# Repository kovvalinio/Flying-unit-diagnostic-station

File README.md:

# Flying-unit-diagnostic-station
This is the development repository for the embedded system created by me and Adam Polus as a diploma thesis.
The goal is to create the system that will collect data from sensors and pass them wirlessly to PC. 
The system will be attached to a drone and will constantly provide data from accelerometers and microphones.
Data will held the information about vibrations generated by motors.

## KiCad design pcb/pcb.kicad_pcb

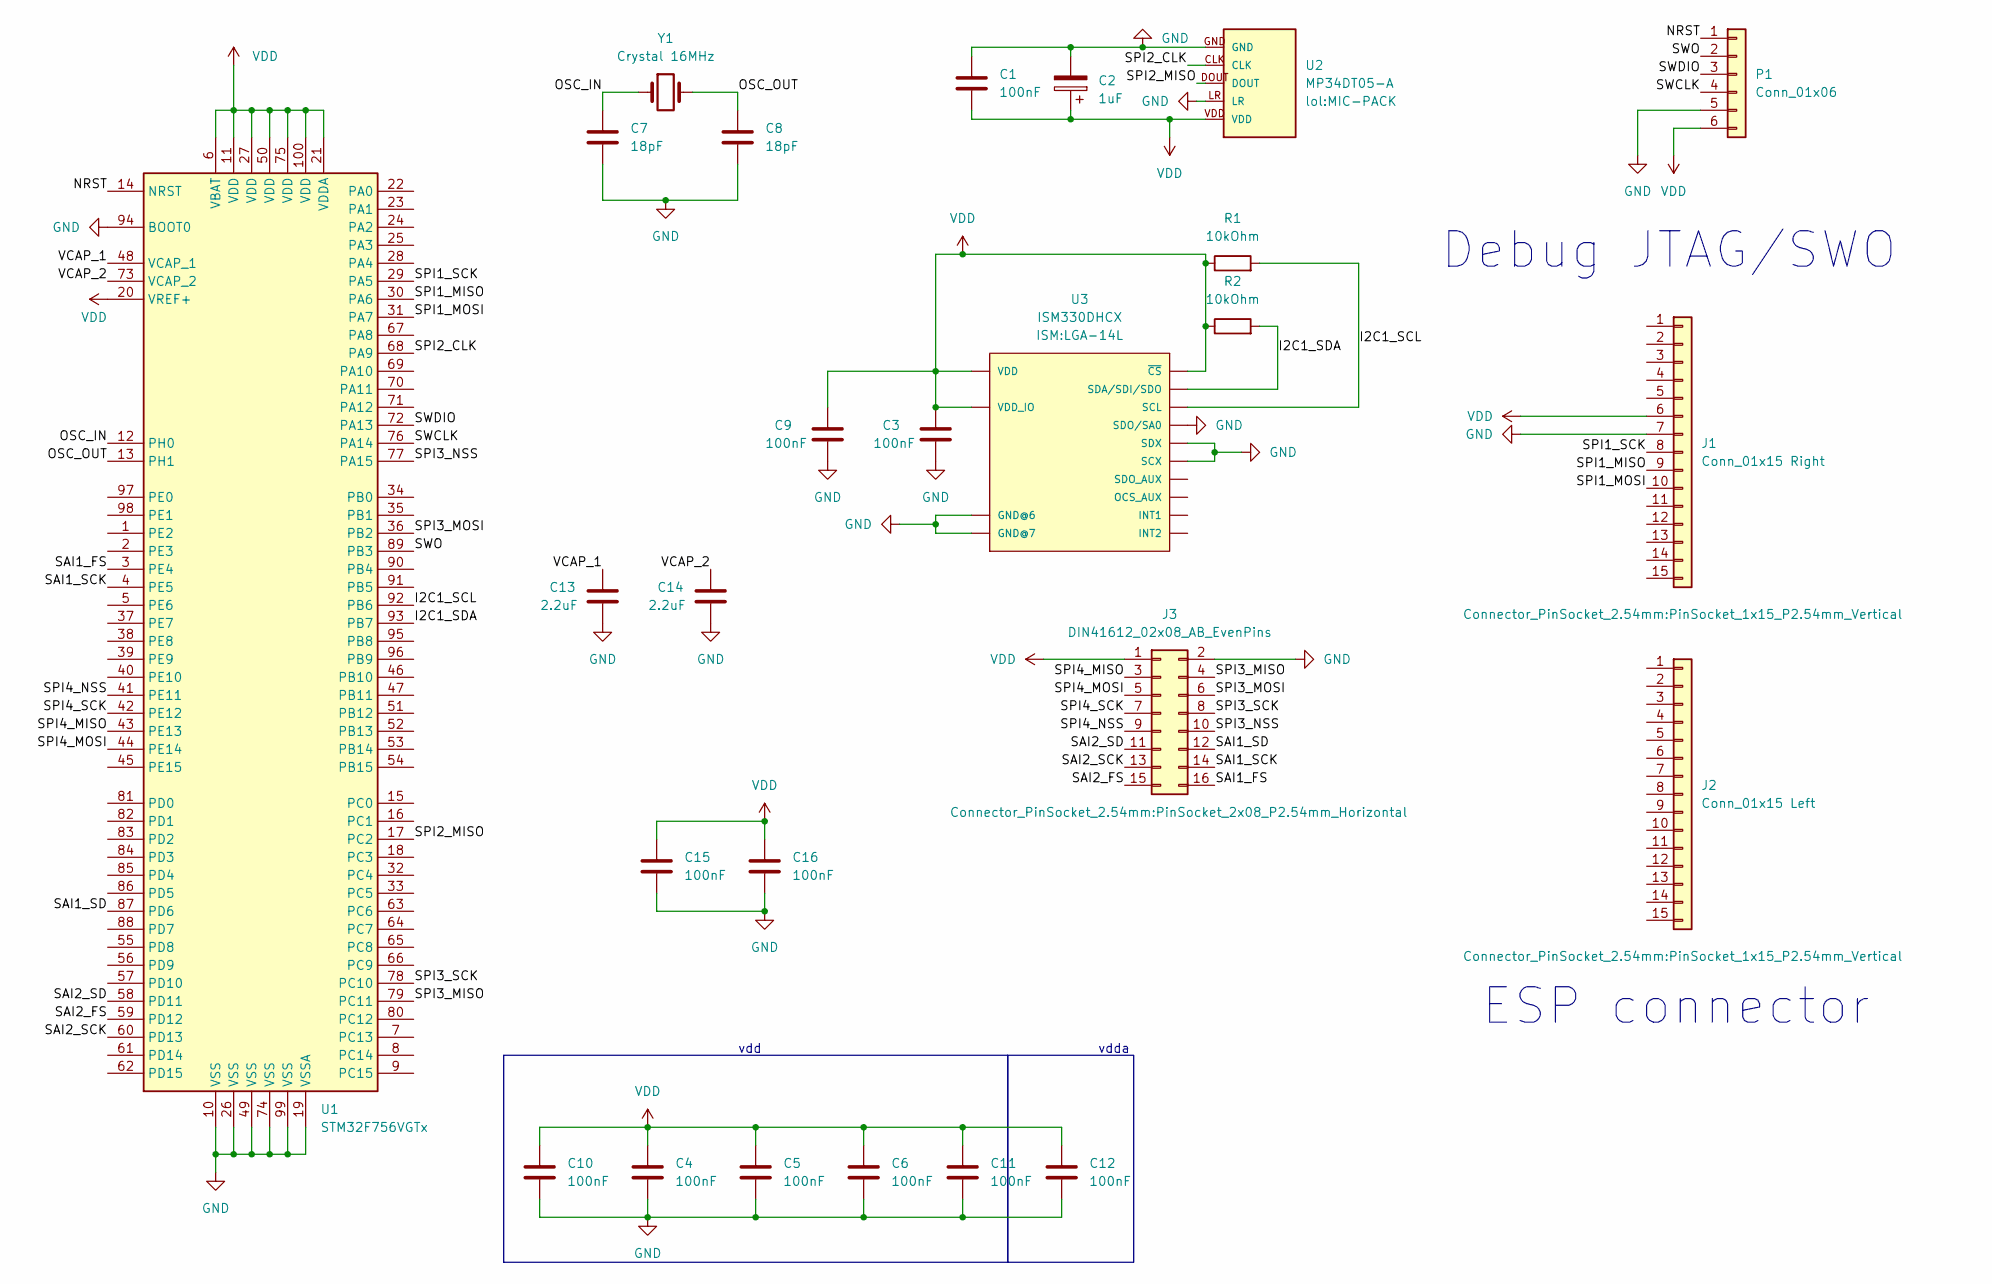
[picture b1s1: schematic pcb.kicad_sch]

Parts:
C1, C4, C5, C6, C10, C11, C12, C15, C16: 100nF; C_0603_1608Metric
C2: 1uF; C_0603_1608Metric
C3, C9: 100nF; R_0603_1608Metric
C7, C8: 18pF; C_0603_1608Metric
C13, C14: 2.2uF; R_0603_1608Metric
J1: Conn_01x15 Right; PinSocket_1x15_P2.54mm_Vertical
J2: Conn_01x15 Left; PinSocket_1x15_P2.54mm_Vertical
J3: DIN41612_02x08_AB_EvenPins; PinSocket_2x08_P2.54mm_Horizontal
P1: Conn_01x06; Molex_PicoBlade_53047-0610_1x06_P1.25mm_Vertical
R1, R2: 10kOhm; R_0603_1608Metric
U1: STM32F756VGTx; LQFP-100_14x14mm_P0.5mm
U2: MP34DT05-A; MIC-PACK
U3: ISM330DHCX; LGA-14L
Y1: Crystal 16MHz; Crystal_SMD_Abracon_ABM3-2Pin_5.0x3.2mm

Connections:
/I2C1_SCL: R1.2, U1.92 (PB6), U3.P13 (SCL)
/I2C1_SDA: R2.2, U1.93 (PB7), U3.P14 (SDA/SDI/SDO)
/NRST: P1.1, U1.14 (NRST)
/OSC_IN: C7.2, U1.12 (PH0), Y1.1
/OSC_OUT: C8.2, U1.13 (PH1), Y1.2
/SAI1_FS: J3.16 (Pin_b16), U1.3 (PE4)
/SAI1_SCK: J3.14 (Pin_b14), U1.4 (PE5)
/SAI1_SD: J3.12 (Pin_b12), U1.87 (PD6)
/SAI2_FS: J3.15 (Pin_a16), U1.59 (PD12)
/SAI2_SCK: J3.13 (Pin_a14), U1.60 (PD13)
/SAI2_SD: J3.11 (Pin_a12), U1.58 (PD11)
/SPI1_MISO: J1.9, U1.30 (PA6)
/SPI1_MOSI: J1.10, U1.31 (PA7)
/SPI1_SCK: J1.8, U1.29 (PA5)
/SPI2_CLK: U1.68 (PA9), U2.CLK
/SPI2_MISO: U1.17 (PC2), U2.DOUT
/SPI3_MISO: J3.4 (Pin_b4), U1.79 (PC11)
/SPI3_MOSI: J3.6 (Pin_b6), U1.36 (PB2)
/SPI3_NSS: J3.10 (Pin_b10), U1.77 (PA15)
/SPI3_SCK: J3.8 (Pin_b8), U1.78 (PC10)
/SPI4_MISO: J3.3 (Pin_a4), U1.43 (PE13)
/SPI4_MOSI: J3.5 (Pin_a6), U1.44 (PE14)
/SPI4_NSS: J3.9 (Pin_a10), U1.41 (PE11)
/SPI4_SCK: J3.7 (Pin_a8), U1.42 (PE12)
/SWCLK: P1.4, U1.76 (PA14)
/SWDIO: P1.3, U1.72 (PA13)
/SWO: P1.2, U1.89 (PB3)
/VCAP_1: C13.1, U1.48 (VCAP_1)
/VCAP_2: C14.1, U1.73 (VCAP_2)
GND: C1.2, C2.2, C3.2, C4.1, C5.1, C6.1, C7.1, C8.1, C9.2, C10.1, C11.1, C12.1, C13.2, C14.2, C15.1, C16.1, J1.7, J3.2 (Pin_b2), P1.5, U1.10 (VSS), U1.19 (VSSA), U1.26 (VSS), U1.49 (VSS), U1.74 (VSS), U1.94 (BOOT0), U1.99 (VSS), U2.GND, U2.LR, U3.P1 (SDO/SA0), U3.P2 (SDX), U3.P3 (SCX), U3.P6 (GND@6), U3.P7 (GND@7)
VDD: C1.1, C2.1, C3.1, C4.2, C5.2, C6.2, C9.1, C10.2, C11.2, C12.2, C15.2, C16.2, J1.6, J3.1 (Pin_a2), P1.6, R1.1, R2.1, U1.6 (VBAT), U1.11 (VDD), U1.20 (VREF+), U1.21 (VDDA), U1.27 (VDD), U1.50 (VDD), U1.75 (VDD), U1.100 (VDD), U2.VDD, U3.P5 (VDD_IO), U3.P8 (VDD), U3.P12 (~CS)

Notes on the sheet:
ESP connector
vdd
Debug JTAG/SWO
vdda

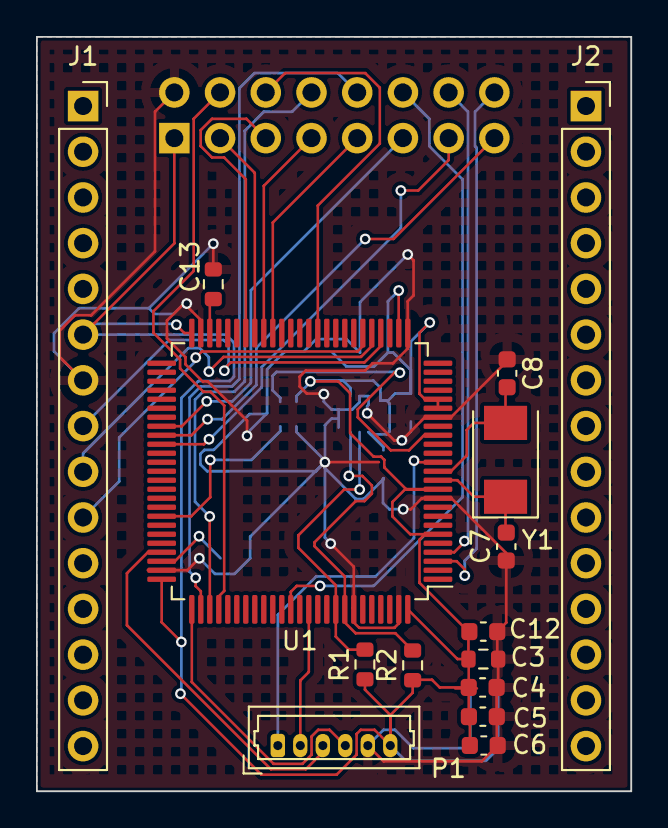
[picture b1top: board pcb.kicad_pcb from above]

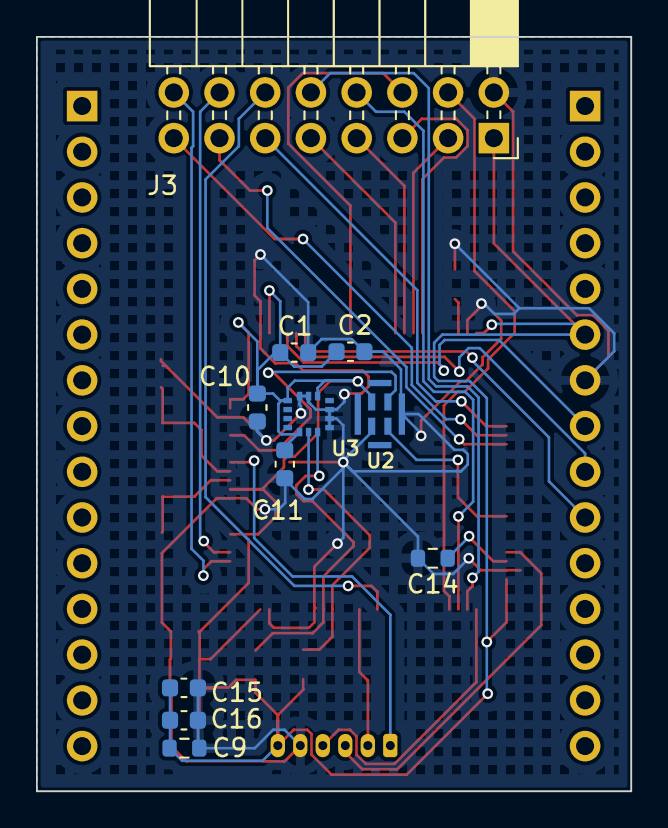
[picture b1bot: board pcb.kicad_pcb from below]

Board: 2 copper layers, 33.0 x 41.9 mm, 26 parts (11 on the bottom side), 31 nets.

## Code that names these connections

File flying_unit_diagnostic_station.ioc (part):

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Mcu.Name=STM32F767ZITx
Mcu.Package=LQFP144
Mcu.UserName=STM32F767ZITx
PA1.GPIOParameters=GPIO_Label
PA1.GPIO_Label=RMII_REF_CLK [LAN8742A-CZ-TR_REFCLK0]
PA1.Signal=ETH_REF_CLK
PA10.GPIOParameters=GPIO_Label
PA10.GPIO_Label=USB_ID
PA10.Signal=USB_OTG_FS_ID
PA11.GPIOParameters=GPIO_Label
PA11.GPIO_Label=USB_DM
PA11.Signal=USB_OTG_FS_DM
PA12.GPIOParameters=GPIO_Label
PA12.GPIO_Label=USB_DP
PA12.Signal=USB_OTG_FS_DP
PA13.GPIOParameters=GPIO_Label
PA13.GPIO_Label=TMS
PA13.Mode=Serial_Wire
PA13.Signal=SYS_JTMS-SWDIO
PA14.GPIOParameters=GPIO_Label
PA14.GPIO_Label=TCK
PA14.Mode=Serial_Wire
PA14.Signal=SYS_JTCK-SWCLK
PA2.GPIOParameters=GPIO_Label
PA2.GPIO_Label=RMII_MDIO [LAN8742A-CZ-TR_MDIO]
PA2.Signal=ETH_MDIO
PA4.Mode=Half_Duplex_Master
PA4.Signal=I2S1_WS
PA5.Mode=Half_Duplex_Master
PA5.Signal=I2S1_CK
PA7.GPIOParameters=GPIO_Label
PA7.GPIO_Label=RMII_CRS_DV [LAN8742A-CZ-TR_CRS_DV]
PA7.Signal=ETH_CRS_DV
PA8.GPIOParameters=GPIO_Label
PA8.GPIO_Label=USB_SOF [TP1]
PA8.Signal=USB_OTG_FS_SOF
PA9.GPIOParameters=GPIO_Label
PA9.GPIO_Label=USB_VBUS
PA9.Signal=USB_OTG_FS_VBUS
PB0.GPIOParameters=GPIO_Label
PB0.GPIO_Label=LD1 [Green]
PB0.Signal=GPIO_Output
PB13.GPIOParameters=GPIO_Label
PB13.GPIO_Label=RMII_TXD1 [LAN8742A-CZ-TR_TXD1]
PB13.Signal=ETH_TXD1
PB14.GPIOParameters=GPIO_Label
PB14.GPIO_Label=LD3 [Red]
PB14.Signal=GPIO_Output
PB3.GPIOParameters=GPIO_Label
PB3.GPIO_Label=SWO
PB3.Signal=SYS_JTDO-SWO
PB7.GPIOParameters=GPIO_Label
PB7.GPIO_Label=LD2 [Blue]
PB7.Signal=GPIO_Output
PB8.Mode=I2C
PB8.Signal=I2C1_SCL
PB9.Mode=I2C
PB9.Signal=I2C1_SDA
PC1.GPIOParameters=GPIO_Label
PC1.GPIO_Label=RMII_MDC [LAN8742A-CZ-TR_MDC]
PC1.Signal=ETH_MDC
PC13.GPIOParameters=GPIO_Label
PC13.GPIO_Label=USER_Btn [B1]
PC13.Signal=GPXTI13
PC14/OSC32_IN.Mode=LSE-External-Oscillator
PC14/OSC32_IN.Signal=RCC_OSC32_IN
PC15/OSC32_OUT.Mode=LSE-External-Oscillator
PC15/OSC32_OUT.Signal=RCC_OSC32_OUT
PC5.GPIOParameters=GPIO_Label
PC5.GPIO_Label=RMII_RXD1 [LAN8742A-CZ-TR_RXD1]
PC5.Signal=ETH_RXD1
PD7.Mode=Half_Duplex_Master
PD7.Signal=I2S1_SD
PD8.GPIOParameters=GPIO_Label
PD8.GPIO_Label=STLK_RX [STM32F103CBT6_PA3]
PD8.Mode=Asynchronous
PD8.Signal=USART3_TX
PD9.GPIOParameters=GPIO_Label
PD9.GPIO_Label=STLK_TX [STM32F103CBT6_PA2]
PD9.Mode=Asynchronous
PD9.Signal=USART3_RX
PF0.Mode=I2C
PF0.Signal=I2C2_SDA
PF1.Mode=I2C
PF1.Signal=I2C2_SCL
PG11.GPIOParameters=GPIO_Label
PG11.GPIO_Label=RMII_TX_EN [LAN8742A-CZ-TR_TXEN]
PG11.Signal=ETH_TX_EN
PG13.GPIOParameters=GPIO_Label
PG13.GPIO_Label=RMII_TXD0 [LAN8742A-CZ-TR_TXD0]
PG13.Signal=ETH_TXD0
PG6.GPIOParameters=GPIO_Label
PG6.GPIO_Label=USB_PowerSwitchOn [STMPS2151STR_EN]
PG6.Signal=GPIO_Output
PG7.GPIOParameters=GPIO_Label
PG7.GPIO_Label=USB_OverCurrent [STMPS2151STR_FAULT]
PG7.Signal=GPIO_Input
PH0/OSC_IN.GPIOParameters=GPIO_Label
PH0/OSC_IN.GPIO_Label=MCO [STM32F103CBT6_PA8]
PH0/OSC_IN.Mode=HSE-External-Clock-Source
PH0/OSC_IN.Signal=RCC_OSC_IN
PH1/OSC_OUT.Mode=HSE-External-Clock-Source
PH1/OSC_OUT.Signal=RCC_OSC_OUT
RCC.HSE_VALUE=8000000
RCC.SYSCLKFreq_VALUE=100000000
RCC.SYSCLKSource=RCC_SYSCLKSOURCE_PLLCLK
RCC.SYSCLKSourceVirtual=RCC_SYSCLKSOURCE_PLLCLK
board=NUCLEO-F767ZI
boardIOC=true

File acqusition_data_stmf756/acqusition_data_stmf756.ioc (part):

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Mcu.Name=STM32F756VGTx
Mcu.Package=LQFP100
Mcu.UserName=STM32F756VGTx
PA1.Mode=Asynchronous
PA1.Signal=UART4_RX
PA6.Signal=GPXTI6
PA7.GPIOParameters=GPIO_PuPd
PA7.GPIO_PuPd=GPIO_PULLDOWN
PA7.Signal=GPIO_Input
PA9.GPIOParameters=GPIO_PuPd
PA9.GPIO_PuPd=GPIO_NOPULL
PA9.Mode=RX_Only_Simplex_Unidirect_Master
PA9.Signal=SPI2_SCK
PB3.Signal=GPIO_Output
PB6.Mode=I2C
PB6.Signal=I2C1_SCL
PB7.Mode=I2C
PB7.Signal=I2C1_SDA
PC10.Mode=Asynchronous
PC10.Signal=UART4_TX
PC2.GPIOParameters=GPIO_PuPd
PC2.GPIO_PuPd=GPIO_NOPULL
PC2.Mode=RX_Only_Simplex_Unidirect_Master
PC2.Signal=SPI2_MISO
PD12.Mode=I2C
PD12.Signal=I2C4_SCL
PD13.Mode=I2C
PD13.Signal=I2C4_SDA
PD5.Signal=GPXTI5
PE0.Mode=Asynchronous
PE0.Signal=UART8_RX
PE1.Mode=Asynchronous
PE1.Signal=UART8_TX
RCC.HSE_VALUE=16000000
RCC.SYSCLKFreq_VALUE=61142857.14285715
RCC.SYSCLKSource=RCC_SYSCLKSOURCE_PLLCLK
board=custom

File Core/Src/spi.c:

/* USER CODE BEGIN Header */
/**
  ******************************************************************************
  * @file    spi.c
  * @brief   This file provides code for the configuration
  *          of the SPI instances.
  ******************************************************************************
  * @attention
  *
  * Copyright (c) 2022 STMicroelectronics.
  * All rights reserved.
  *
  * This software is licensed under terms that can be found in the LICENSE file
  * in the root directory of this software component.
  * If no LICENSE file comes with this software, it is provided AS-IS.
  *
  ******************************************************************************
  */
/* USER CODE END Header */
/* Includes ------------------------------------------------------------------*/
#include "spi.h"

/* USER CODE BEGIN 0 */

/* USER CODE END 0 */

SPI_HandleTypeDef hspi1;
DMA_HandleTypeDef hdma_spi1_rx;

/* SPI1 init function */
void MX_SPI1_Init(void)
{

  /* USER CODE BEGIN SPI1_Init 0 */

  /* USER CODE END SPI1_Init 0 */

  /* USER CODE BEGIN SPI1_Init 1 */

  /* USER CODE END SPI1_Init 1 */
  hspi1.Instance = SPI1;
  hspi1.Init.Mode = SPI_MODE_MASTER;
  hspi1.Init.Direction = SPI_DIRECTION_2LINES_RXONLY;
  hspi1.Init.DataSize = SPI_DATASIZE_8BIT;
  hspi1.Init.CLKPolarity = SPI_POLARITY_LOW;
  hspi1.Init.CLKPhase = SPI_PHASE_1EDGE;
  hspi1.Init.NSS = SPI_NSS_SOFT;
  hspi1.Init.BaudRatePrescaler = SPI_BAUDRATEPRESCALER_16;
  hspi1.Init.FirstBit = SPI_FIRSTBIT_MSB;
  hspi1.Init.TIMode = SPI_TIMODE_DISABLE;
  hspi1.Init.CRCCalculation = SPI_CRCCALCULATION_DISABLE;
  hspi1.Init.CRCPolynomial = 7;
  hspi1.Init.CRCLength = SPI_CRC_LENGTH_DATASIZE;
  hspi1.Init.NSSPMode = SPI_NSS_PULSE_ENABLE;
  if (HAL_SPI_Init(&hspi1) != HAL_OK)
  {
    Error_Handler();
  }
  /* USER CODE BEGIN SPI1_Init 2 */

  /* USER CODE END SPI1_Init 2 */

}

void HAL_SPI_MspInit(SPI_HandleTypeDef* spiHandle)
{

  GPIO_InitTypeDef GPIO_InitStruct = {0};
  if(spiHandle->Instance==SPI1)
  {
  /* USER CODE BEGIN SPI1_MspInit 0 */

  /* USER CODE END SPI1_MspInit 0 */
    /* SPI1 clock enable */
    __HAL_RCC_SPI1_CLK_ENABLE();

    __HAL_RCC_GPIOA_CLK_ENABLE();
    /**SPI1 GPIO Configuration
    PA5     ------> SPI1_SCK
    PA6     ------> SPI1_MISO
    */
    GPIO_InitStruct.Pin = GPIO_PIN_5|GPIO_PIN_6;
    GPIO_InitStruct.Mode = GPIO_MODE_AF_PP;
    GPIO_InitStruct.Pull = GPIO_NOPULL;
    GPIO_InitStruct.Speed = GPIO_SPEED_FREQ_VERY_HIGH;
    GPIO_InitStruct.Alternate = GPIO_AF5_SPI1;
    HAL_GPIO_Init(GPIOA, &GPIO_InitStruct);

    /* SPI1 DMA Init */
    /* SPI1_RX Init */
    hdma_spi1_rx.Instance = DMA2_Stream0;
    hdma_spi1_rx.Init.Channel = DMA_CHANNEL_3;
    hdma_spi1_rx.Init.Direction = DMA_PERIPH_TO_MEMORY;
    hdma_spi1_rx.Init.PeriphInc = DMA_PINC_DISABLE;
    hdma_spi1_rx.Init.MemInc = DMA_MINC_ENABLE;
    hdma_spi1_rx.Init.PeriphDataAlignment = DMA_PDATAALIGN_BYTE;
    hdma_spi1_rx.Init.MemDataAlignment = DMA_MDATAALIGN_BYTE;
    hdma_spi1_rx.Init.Mode = DMA_CIRCULAR;
    hdma_spi1_rx.Init.Priority = DMA_PRIORITY_LOW;
    hdma_spi1_rx.Init.FIFOMode = DMA_FIFOMODE_ENABLE;
    hdma_spi1_rx.Init.FIFOThreshold = DMA_FIFO_THRESHOLD_FULL;
    hdma_spi1_rx.Init.MemBurst = DMA_MBURST_SINGLE;
    hdma_spi1_rx.Init.PeriphBurst = DMA_PBURST_SINGLE;
    if (HAL_DMA_Init(&hdma_spi1_rx) != HAL_OK)
    {
      Error_Handler();
    }

    __HAL_LINKDMA(spiHandle,hdmarx,hdma_spi1_rx);

  /* USER CODE BEGIN SPI1_MspInit 1 */

  /* USER CODE END SPI1_MspInit 1 */
  }
}

void HAL_SPI_MspDeInit(SPI_HandleTypeDef* spiHandle)
{

  if(spiHandle->Instance==SPI1)
  {
  /* USER CODE BEGIN SPI1_MspDeInit 0 */

  /* USER CODE END SPI1_MspDeInit 0 */
    /* Peripheral clock disable */
    __HAL_RCC_SPI1_CLK_DISABLE();

    /**SPI1 GPIO Configuration
    PA5     ------> SPI1_SCK
    PA6     ------> SPI1_MISO
    */
    HAL_GPIO_DeInit(GPIOA, GPIO_PIN_5|GPIO_PIN_6);

    /* SPI1 DMA DeInit */
    HAL_DMA_DeInit(spiHandle->hdmarx);
  /* USER CODE BEGIN SPI1_MspDeInit 1 */

  /* USER CODE END SPI1_MspDeInit 1 */
  }
}

/* USER CODE BEGIN 1 */

/* USER CODE END 1 */

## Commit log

2022-09-14 read_values_function_implementation
2022-09-22 microphone_data_read_added
2022-09-26 Esp_program_and_connection.
2022-09-26 ESP add instructions
2022-10-13 tests1
2022-10-13 test1
2022-10-18 pcb_0
2022-11-14 pcb_1
2022-11-14 pcb_2
2022-11-16 pcb_3
2022-11-16 pcb_4
2022-11-16 pcb_5
2022-11-17 pcb_6
2022-11-22 pcb_7
2022-11-22 pcb_8
2022-11-23 pcb_9
2022-11-23 pcb_10
2022-11-24 pcb_11
2023-02-04 working_stm_part
2023-02-04 dirs_for_other_parts
2023-02-04 reedme
2023-02-04 Esp code and ground station application code
